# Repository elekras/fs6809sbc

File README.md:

# fs6809sbc
A simple 6809 single board computer under 
Open Source Hardware (OSHW) Definition 1.0
https://www.oshwa.org/definition/
by Fabio Sturman (c) 2024 fabio.sturman@gmail.com

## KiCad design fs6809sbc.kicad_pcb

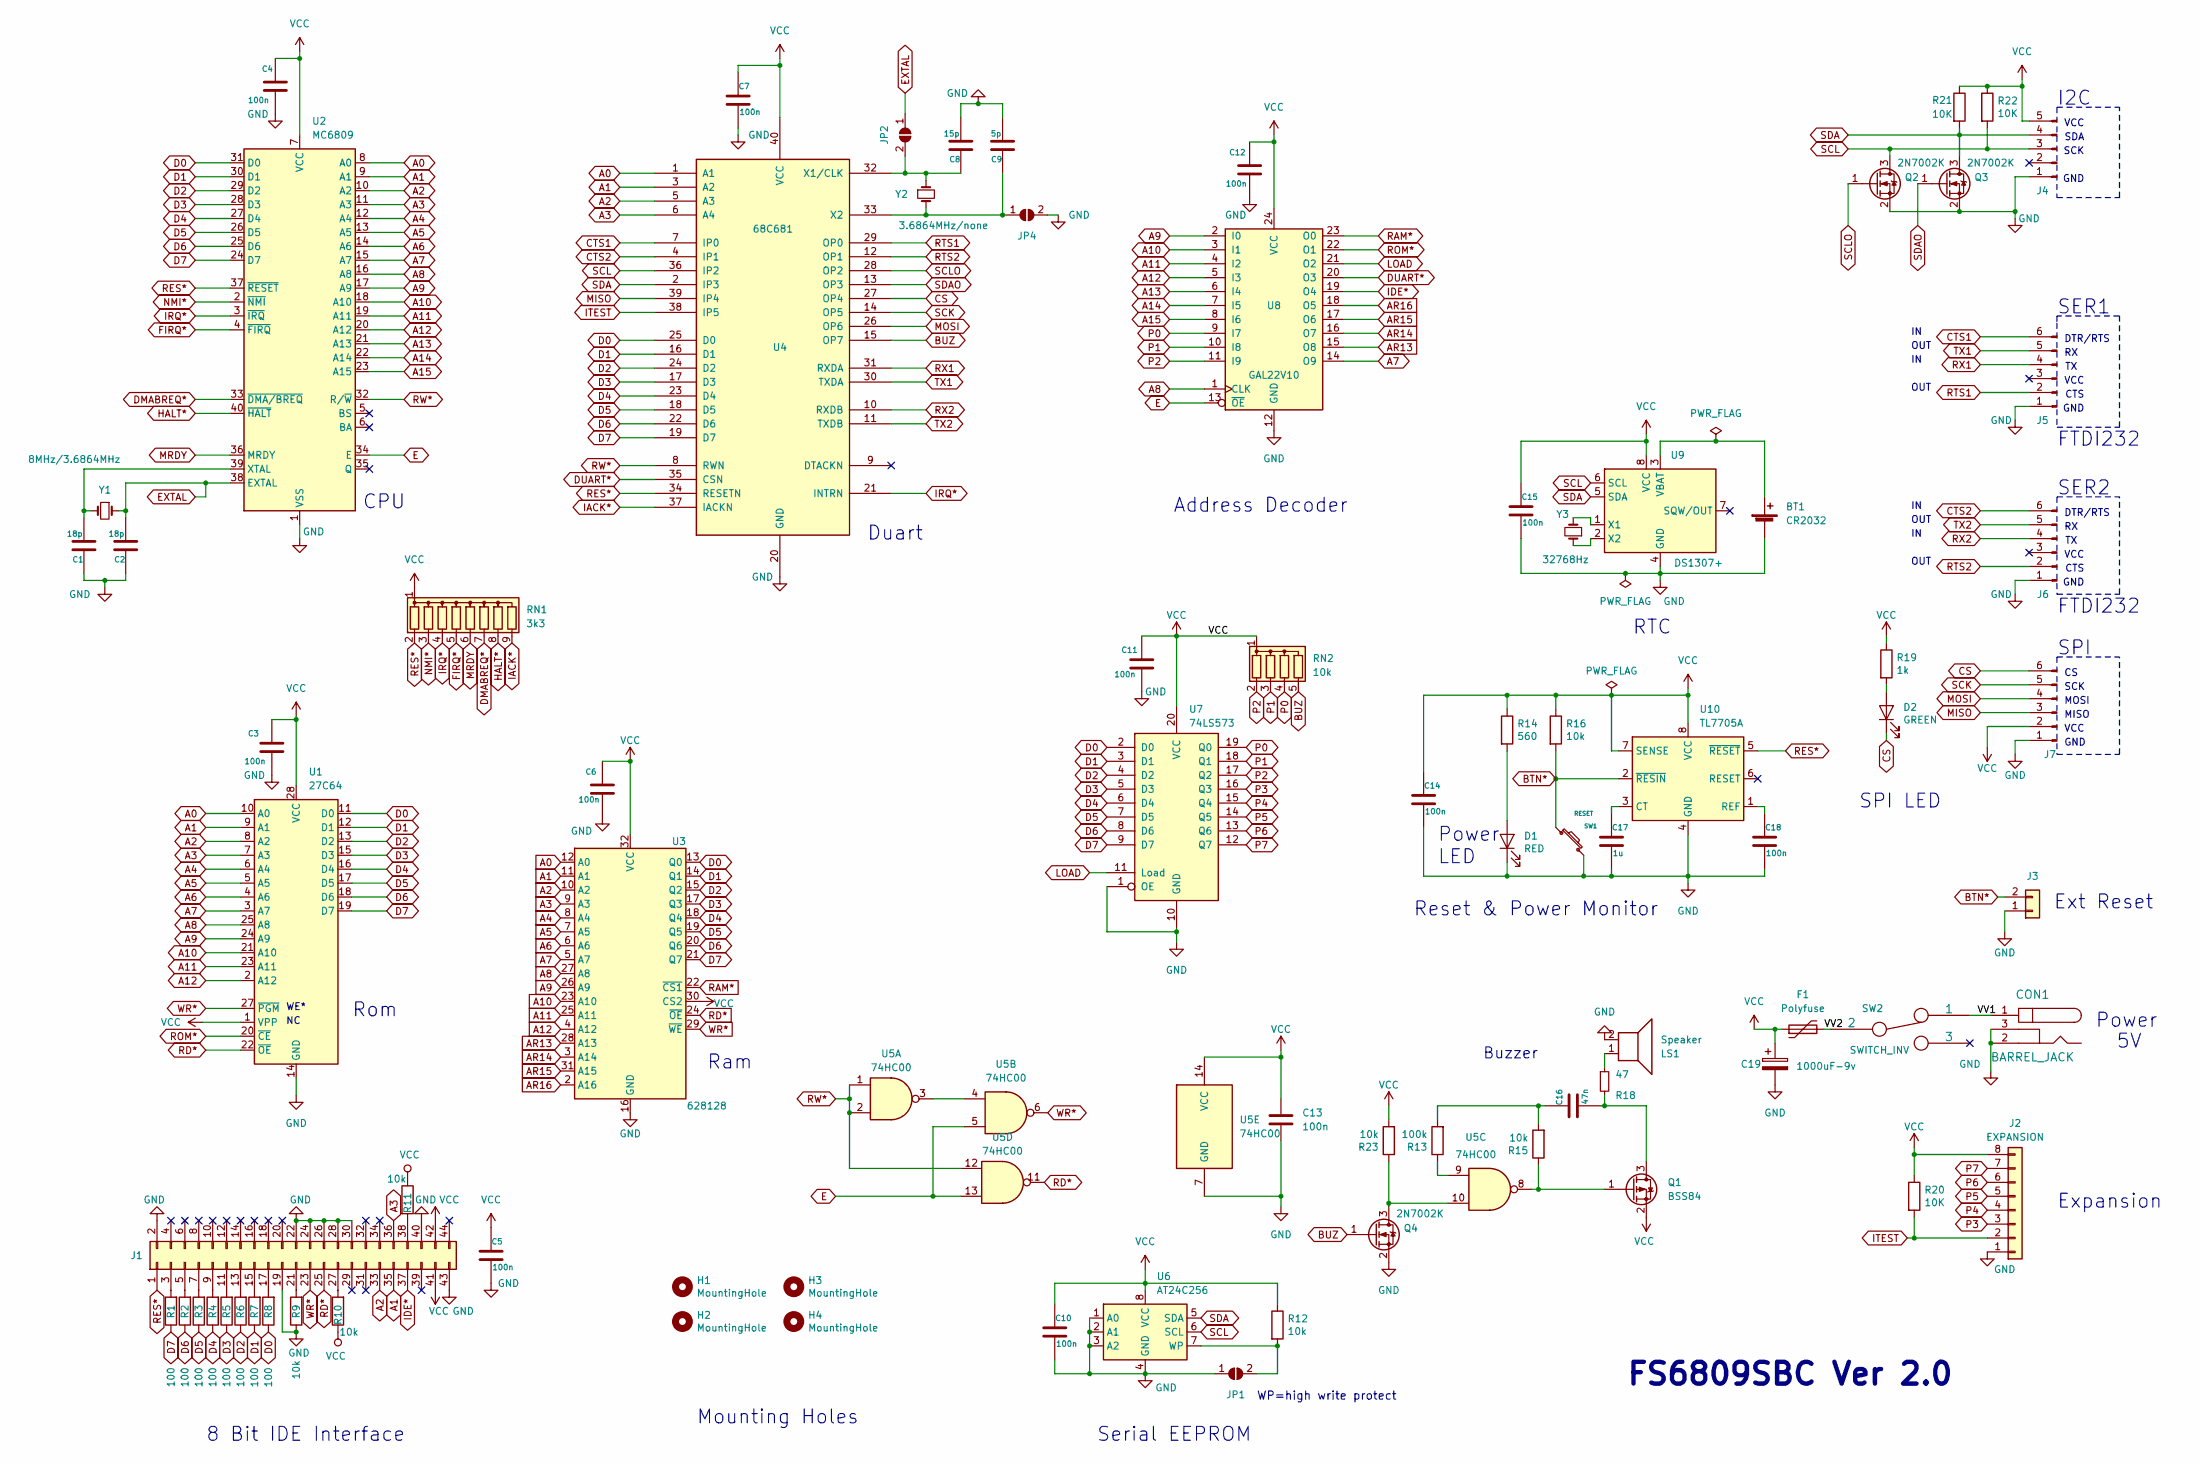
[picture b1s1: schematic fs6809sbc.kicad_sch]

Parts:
BT1: CR2032; Battery_CR2032-HFN_Horizontal_CircularHoles
C1, C2: 18p; C_0805_2012Metric_Pad1.18x1.45mm_HandSolder
C3, C4, C5, C6, C7, C10, C11, C12, C13, C14, C15, C18: 100n; C_0805_2012Metric_Pad1.18x1.45mm_HandSolder
C8: 15p; C_0805_2012Metric_Pad1.18x1.45mm_HandSolder
C9: 5p; C_0805_2012Metric_Pad1.18x1.45mm_HandSolder
C16: 47n; C_0805_2012Metric_Pad1.18x1.45mm_HandSolder
C17: 1u; C_0805_2012Metric_Pad1.18x1.45mm_HandSolder
C19: 1000uF-9v; CP_Radial_D8.0mm_P2.50mm
CON1: BARREL_JACK; BarrelJack_Wuerth_6941xx301002
D1: RED; LED_0805_2012Metric_Pad1.15x1.40mm_HandSolder
D2: GREEN; LED_0805_2012Metric_Pad1.15x1.40mm_HandSolder
F1: Polyfuse; D_SMB_Handsoldering
H1, H2, H3, H4: MountingHole; MountingHole_3.5mm_Pad
J1: Conn_02x22_Odd_Even; Edge_2x22_P2.00mm_SMD
J2: EXPANSION; PinHeader_1x08_P2.54mm_Vertical
J3: RESET; PinHeader_1x02_P2.54mm_Vertical
J4: I2C; PinHeader_1x05_P2.54mm_Vertical
J5: SER1; PinHeader_1x06_P2.54mm_Vertical
J6: SER2; PinHeader_1x06_P2.54mm_Vertical
J7: SPI; PinHeader_1x06_P2.54mm_Vertical
JP1, JP2, JP4: SolderJumper_2_Open; SolderJumper-2_P1.3mm_Open_RoundedPad1.0x1.5mm
LS1: Speaker; Buzzer_12x9.5RM6.5
Q1: BSS84; SOT-23_Handsoldering
Q2, Q3, Q4: 2N7002K; SOT-23_Handsoldering
R1, R2, R3, R4, R5, R6, R7, R8: 100; R_0805_2012Metric_Pad1.20x1.40mm_HandSolder
R9, R10, R11, R12, R15, R16, R23: 10k; R_0805_2012Metric_Pad1.20x1.40mm_HandSolder
R13: 100k; R_0805_2012Metric_Pad1.20x1.40mm_HandSolder
R14: 560; R_0805_2012Metric_Pad1.20x1.40mm_HandSolder
R18: 47; R_0805_2012Metric_Pad1.20x1.40mm_HandSolder
R19: 1k; R_0805_2012Metric_Pad1.20x1.40mm_HandSolder
R20, R21, R22: 10K; R_0805_2012Metric_Pad1.20x1.40mm_HandSolder
RN1: 3k3; R_Array_SIP9
RN2: 10k; R_Array_SIP5
SW1: RESET; SW_PUSH_6mm_H4.3mm
SW2: SWITCH_INV; PinHeader_1x03_P2.54mm_Vertical
U1: 27C64; DIP-28_W15.24mm_Socket_LongPads
U2: MC6809; DIP-40_W15.24mm_Socket_LongPads
U3: 628128; DIP-32_W15.24mm_Socket_LongPads
U4: 68C681; DIP-40_W15.24mm_Socket_LongPads
U5: 74HC00; DIP-14_W7.62mm_Socket_LongPads
U6: AT24C256; DIP-8_W7.62mm_Socket_LongPads
U7: 74LS573; DIP-20_W7.62mm_Socket_LongPads
U8: GAL22V10; DIP-24_W7.62mm_Socket_LongPads
U9: DS1307+; DIP-8_W7.62mm_Socket_LongPads
U10: TL7705A; DIP-8_W7.62mm_Socket_LongPads
Y1: 8MHz/3.6864MHz; Crystal_HC49-U_Vertical
Y2: 3.6864MHz/none; Crystal_HC49-U_Vertical
Y3: 32768Hz; Crystal_AT310_D3.0mm_L10.0mm_Horizontal

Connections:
/VV1: CON1.1, SW2.1
/VV2: F1.2, SW2.2
A0: U1.10 (A0), U2.8 (A0), U3.12 (A0), U4.1 (A1)
A1: J1.35, U1.9 (A1), U2.9 (A1), U3.11 (A1), U4.3 (A2)
A2: J1.33, U1.8 (A2), U2.10 (A2), U3.10 (A2), U4.5 (A3)
A3: J1.36, U1.7 (A3), U2.11 (A3), U3.9 (A3), U4.6 (A4)
A4: U1.6 (A4), U2.12 (A4), U3.8 (A4)
A5: U1.5 (A5), U2.13 (A5), U3.7 (A5)
A6: U1.4 (A6), U2.14 (A6), U3.6 (A6)
A7: U1.3 (A7), U2.15 (A7), U3.5 (A7), U8.14 (O9)
A8: U1.25 (A8), U2.16 (A8), U3.27 (A8), U8.1 (CLK)
A9: U1.24 (A9), U2.17 (A9), U3.26 (A9), U8.2 (I0)
A10: U1.21 (A10), U2.18 (A10), U3.23 (A10), U8.3 (I1)
A11: U1.23 (A11), U2.19 (A11), U3.25 (A11), U8.4 (I2)
A12: U1.2 (A12), U2.20 (A12), U3.4 (A12), U8.5 (I3)
A13: U2.21 (A13), U8.6 (I4)
A14: U2.22 (A14), U8.7 (I5)
A15: U2.23 (A15), U8.8 (I6)
AR13: U3.28 (A13), U8.15 (O8)
AR14: U3.3 (A14), U8.16 (O7)
AR15: U3.31 (A15), U8.17 (O6)
AR16: U3.2 (A16), U8.18 (O5)
BTN*: J3.2, R16.2, SW1.1, U10.2 (~RESIN)
BUZ: Q4.1 (G), RN2.5 (R4), U4.15 (OP7)
CS: D2.1 (K), J7.6, U4.27 (OP4)
CTS1: J5.6, U4.7 (IP0)
CTS2: J6.6, U4.4 (IP1)
D0: R8.1, U1.11 (D0), U2.31 (D0), U3.13 (Q0), U4.25 (D0), U7.2 (D0)
D1: R7.1, U1.12 (D1), U2.30 (D1), U3.14 (Q1), U4.16 (D1), U7.3 (D1)
D2: R6.1, U1.13 (D2), U2.29 (D2), U3.15 (Q2), U4.24 (D2), U7.4 (D2)
D3: R5.1, U1.15 (D3), U2.28 (D3), U3.17 (Q3), U4.17 (D3), U7.5 (D3)
D4: R4.1, U1.16 (D4), U2.27 (D4), U3.18 (Q4), U4.23 (D4), U7.6 (D4)
D5: R3.1, U1.17 (D5), U2.26 (D5), U3.19 (Q5), U4.18 (D5), U7.7 (D5)
D6: R2.1, U1.18 (D6), U2.25 (D6), U3.20 (Q6), U4.22 (D6), U7.8 (D6)
D7: R1.1, U1.19 (D7), U2.24 (D7), U3.21 (Q7), U4.19 (D7), U7.9 (D7)
DMABREQ*: RN1.7 (R6), U2.33 (~DMA/BREQ)
DUART*: U4.35 (CSN), U8.20 (O3)
E: U2.34 (E), U5.5, U5.13, U8.13 (~OE)
EXTAL: C2.2, JP2.1 (A), U2.38 (EXTAL), Y1.1
FIRQ*: RN1.5 (R4), U2.4 (~FIRQ)
GND: BT1.2 (-), C1.1, C2.1, C3.2, C4.2, C5.2, C6.2, C7.2, C8.2, C9.2, C10.2, C11.2, C12.2, C13.2, C14.2, C15.2, C17.2, C18.2, C19.2, CON1.2, CON1.3, D1.1 (K), J1.2, J1.19, J1.22, J1.24, J1.26, J1.28, J1.30, J1.40, J1.43, J2.1, J3.1, J4.1, J5.1, J6.1, J7.1, JP1.1 (A), JP4.2 (B), LS1.2, Q2.2 (S), Q3.2 (S), Q4.2 (S), R9.1, SW1.2, U1.14 (GND), U2.1 (VSS), U3.16 (GND), U4.20 (GND), U5.7 (GND), U6.1 (A0), U6.2 (A1), U6.3 (A2), U6.4 (GND), U7.1 (OE), U7.10 (GND), U8.12 (GND), U9.4 (GND), U10.4 (GND)
HALT*: RN1.8 (R7), U2.40 (~HALT)
IACK*: RN1.9 (R8), U4.37 (IACKN)
IDE*: J1.37, U8.19 (O4)
IRQ*: RN1.4 (R3), U2.3 (~IRQ), U4.21 (INTRN)
ITEST: J2.2, R20.2, U4.38 (IP5)
LOAD: U7.11 (Load), U8.21 (O2)
MISO: J7.3, U4.39 (IP4)
MOSI: J7.4, U4.26 (OP6)
MRDY: RN1.6 (R5), U2.36 (MRDY)
NMI*: RN1.3 (R2), U2.2 (~NMI)
unnamed: BT1.1 (+), U9.3 (VBAT)
unnamed: C16.1, R13.2, R15.2
unnamed: D1.2 (A), R14.2
unnamed: D2.2 (A), R19.2
unnamed: J1.3, R1.2
unnamed: J1.5, R2.2
unnamed: J1.7, R3.2
unnamed: J1.9, R4.2
unnamed: J1.11, R5.2
unnamed: J1.13, R6.2
unnamed: J1.15, R7.2
unnamed: J1.17, R8.2
unnamed: J1.21, R9.2
unnamed: J1.27, R10.2
unnamed: J1.38, R11.2
unnamed: JP1.2 (B), R12.2, U6.7 (WP)
unnamed: C8.1, JP2.2 (B), U4.32 (X1/CLK), Y2.1
unnamed: C9.1, JP4.1 (A), U4.33 (X2), Y2.2
unnamed: LS1.1, R18.1
unnamed: C16.2, Q1.3 (D), R18.2
unnamed: Q1.1 (G), R15.1, U5.8
unnamed: Q4.3 (D), R23.1, U5.10
unnamed: R13.1, U5.9
unnamed: C1.2, U2.39 (XTAL), Y1.2
unnamed: U5.3, U5.4
unnamed: U9.1 (X1), Y3.2
unnamed: U9.2 (X2), Y3.1
unnamed: C17.1, U10.3 (CT)
unnamed: C18.1, U10.1 (REF)
P0: RN2.4 (R3), U7.19 (Q0), U8.9 (I7)
P1: RN2.3 (R2), U7.18 (Q1), U8.10 (I8)
P2: RN2.2 (R1), U7.17 (Q2), U8.11 (I9)
P3: J2.3, U7.16 (Q3)
P4: J2.4, U7.15 (Q4)
P5: J2.5, U7.14 (Q5)
P6: J2.6, U7.13 (Q6)
P7: J2.7, U7.12 (Q7)
RAM*: U3.22 (~CS1), U8.23 (O0)
RD*: J1.25, U1.22 (~OE), U3.24 (~OE), U5.11
RES*: J1.1, RN1.2 (R1), U2.37 (~RESET), U4.34 (RESETN), U10.5 (~RESET)
ROM*: U1.20 (~CE), U8.22 (O1)
RTS1: J5.2, U4.29 (OP0)
RTS2: J6.2, U4.12 (OP1)
RW*: U2.32 (R/~W), U4.8 (RWN), U5.1, U5.2, U5.12
RX1: J5.4, U4.31 (RXDA)
RX2: J6.4, U4.10 (RXDB)
SCK: J7.5, U4.14 (OP5)
SCL: J4.3, Q2.3 (D), R22.2, U4.36 (IP2), U6.6 (SCL), U9.6 (SCL)
SCLO: Q2.1 (G), U4.28 (OP2)
SDA: J4.4, Q3.3 (D), R21.2, U4.2 (IP3), U6.5 (SDA), U9.5 (SDA)
SDAO: Q3.1 (G), U4.13 (OP3)
TX1: J5.5, U4.30 (TXDA)
TX2: J6.5, U4.11 (TXDB)
VCC: C3.1, C4.1, C5.1, C6.1, C7.1, C10.1, C11.1, C12.1, C13.1, C14.1, C15.1, C19.1, F1.1, J1.41, J1.42, J2.8, J4.5, J7.2, Q1.2 (S), R10.1, R11.1, R12.1, R14.1, R16.1, R19.1, R20.1, R21.1, R22.1, R23.2, RN1.1 (common), RN2.1 (common), U1.1 (VPP), U1.28 (VCC), U2.7 (VCC), U3.30 (CS2), U3.32 (VCC), U4.40 (VCC), U5.14 (VCC), U6.8 (VCC), U7.20 (VCC), U8.24 (VCC), U9.8 (VCC), U10.7 (SENSE), U10.8 (VCC)
WR*: J1.23, U1.27 (~PGM), U3.29 (~WE), U5.6

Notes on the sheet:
Duart
CTS
Ext Reset
VCC
OUT
GND
Reset & Power Monitor
CPU
I2C
Buzzer
MOSI
SCK
Mounting Holes
Expansion
Ram
Address Decoder
SDA
DTR/RTS
SER2
Power LED
Serial EEPROM
MISO
SPI LED
Rom
8 Bit IDE Interface
WP=high write protect
Power
WE*
FTDI232
SER1
SPI
FS6809SBC Ver 2.0
RTC

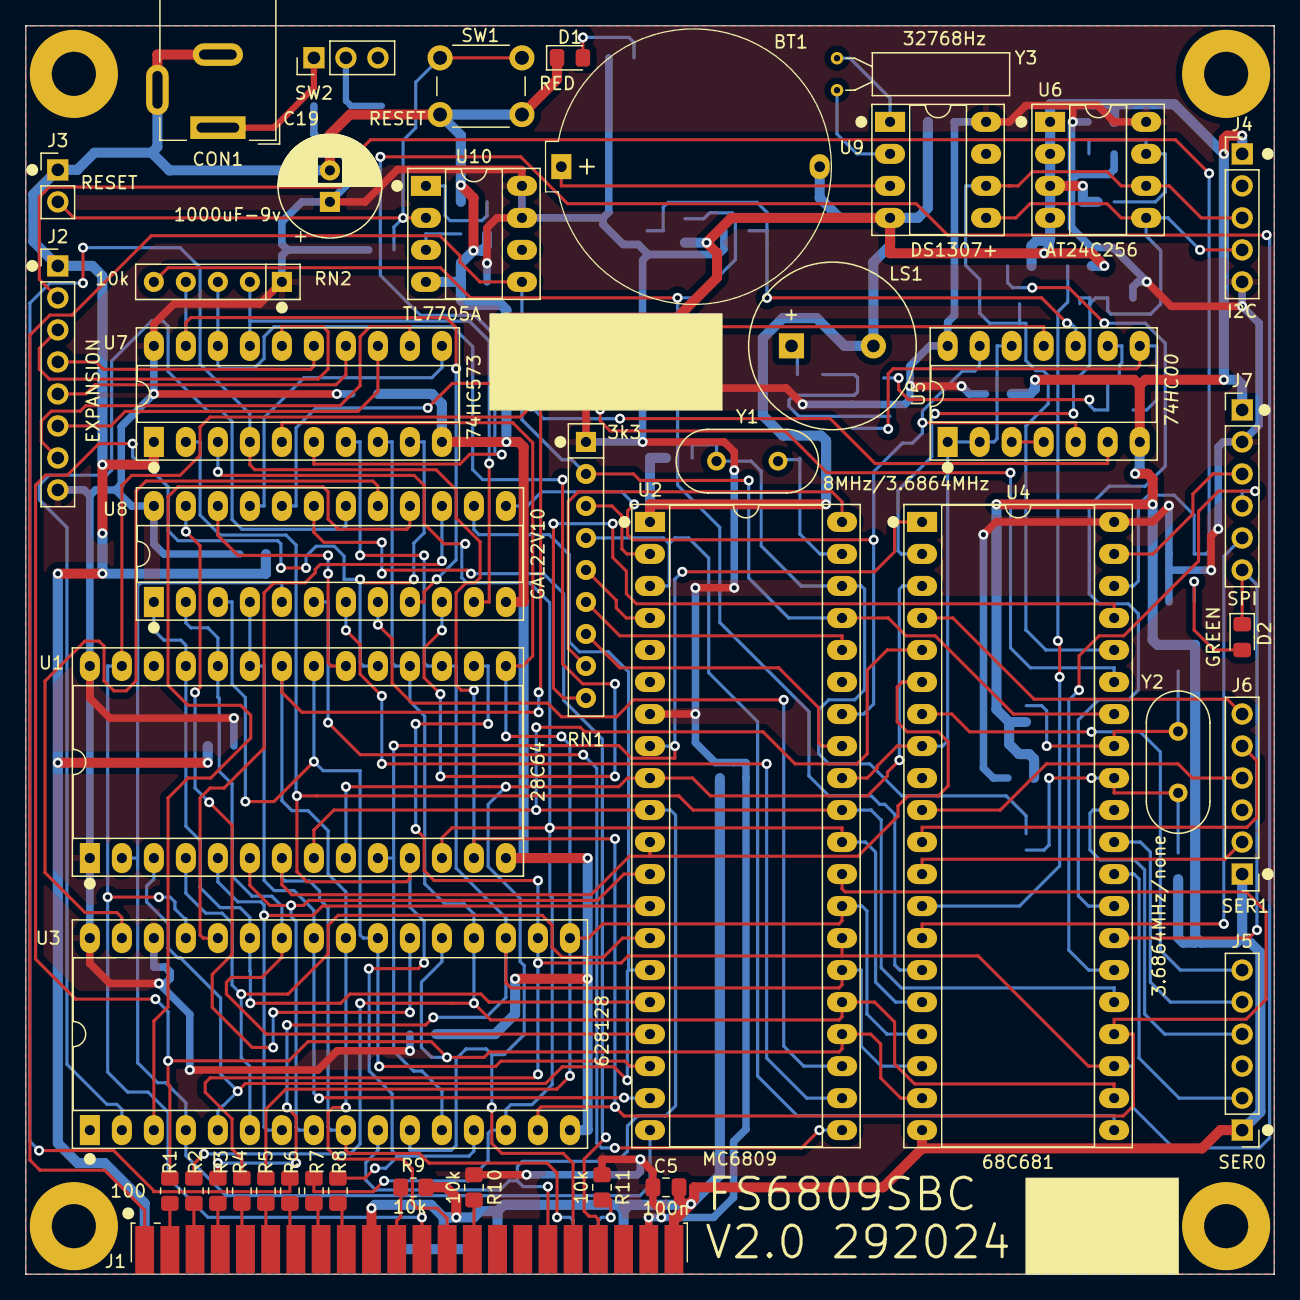
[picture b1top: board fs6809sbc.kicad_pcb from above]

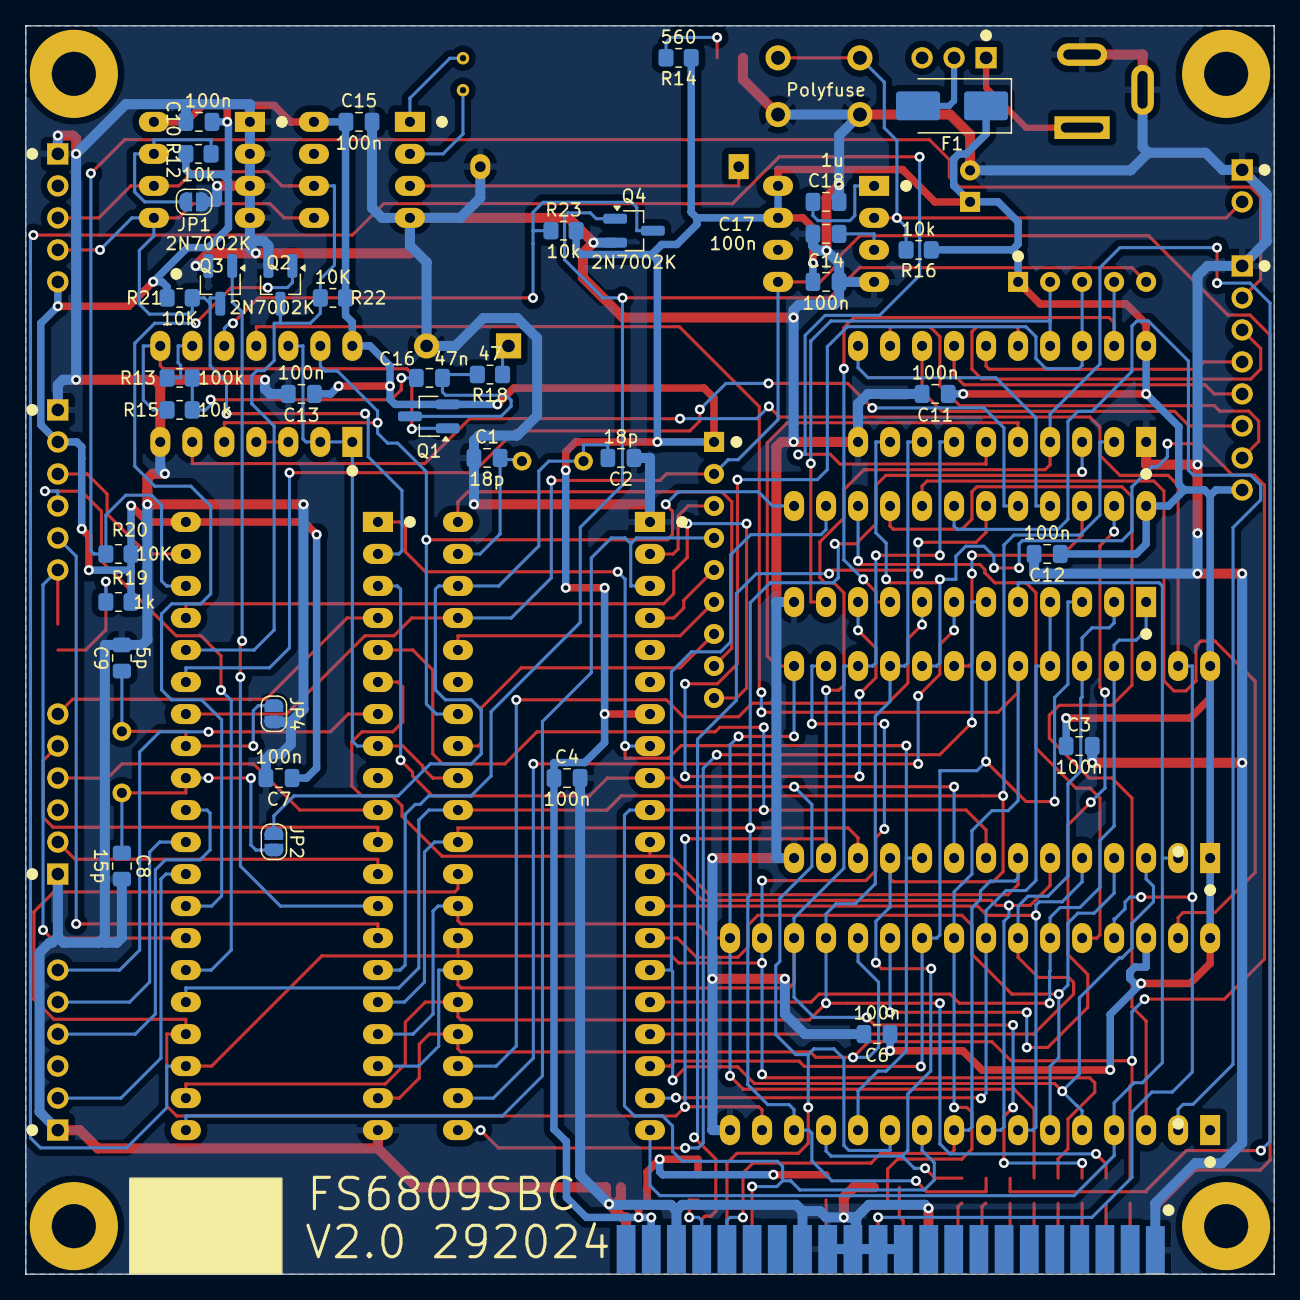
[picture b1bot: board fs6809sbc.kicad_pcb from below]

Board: 2 copper layers, 99.1 x 99.1 mm, 82 parts (36 on the bottom side), 106 nets.
